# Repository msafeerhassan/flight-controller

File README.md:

# Custom Flight Controller
## A completely custom high-efficiency Flight Controller for Drone.
This flight controller is based on STM32F722RET6 MCU and BMI270 Gyro. This is optimized for modern FPV Drones featuring a 4 layer PCB and a dedicated 8-Pin connecter for modern ESC's.

### Hardware Specifications

MCU: STM32F722RET6

Gyro: BMI270 via Serial Peripheral Interface

Storage: W25NO1G

Input Voltage: 3S-6S LiPo (integrated 5V/2A Regulator)

OSD: AT7456E

Features: Buzzer for emergency situation, USB-C Programming, Suitable capacitors, diodes, inductors and resistors

### ESC Connection Guide
Pin 1 : VBAT : Battery Input

Pin 2 : GND : Ground

Pin 3 : Motor 1 : PB4

Pin 4 : Motor 2 : PB5

Pin 5 : Motor 3 : PB0

Pin 6 : Motor 4 : PB1

Pin 7 : Current : PC0

Pin 8 : Telemetry : PC7

### Software Specifications
Compatible with: 
- Betaflight
- Rotorflight
##### Code is given in firmware folder

### PCB:

### Schematic Diagram:

### Designed by Safeer Hassan :)

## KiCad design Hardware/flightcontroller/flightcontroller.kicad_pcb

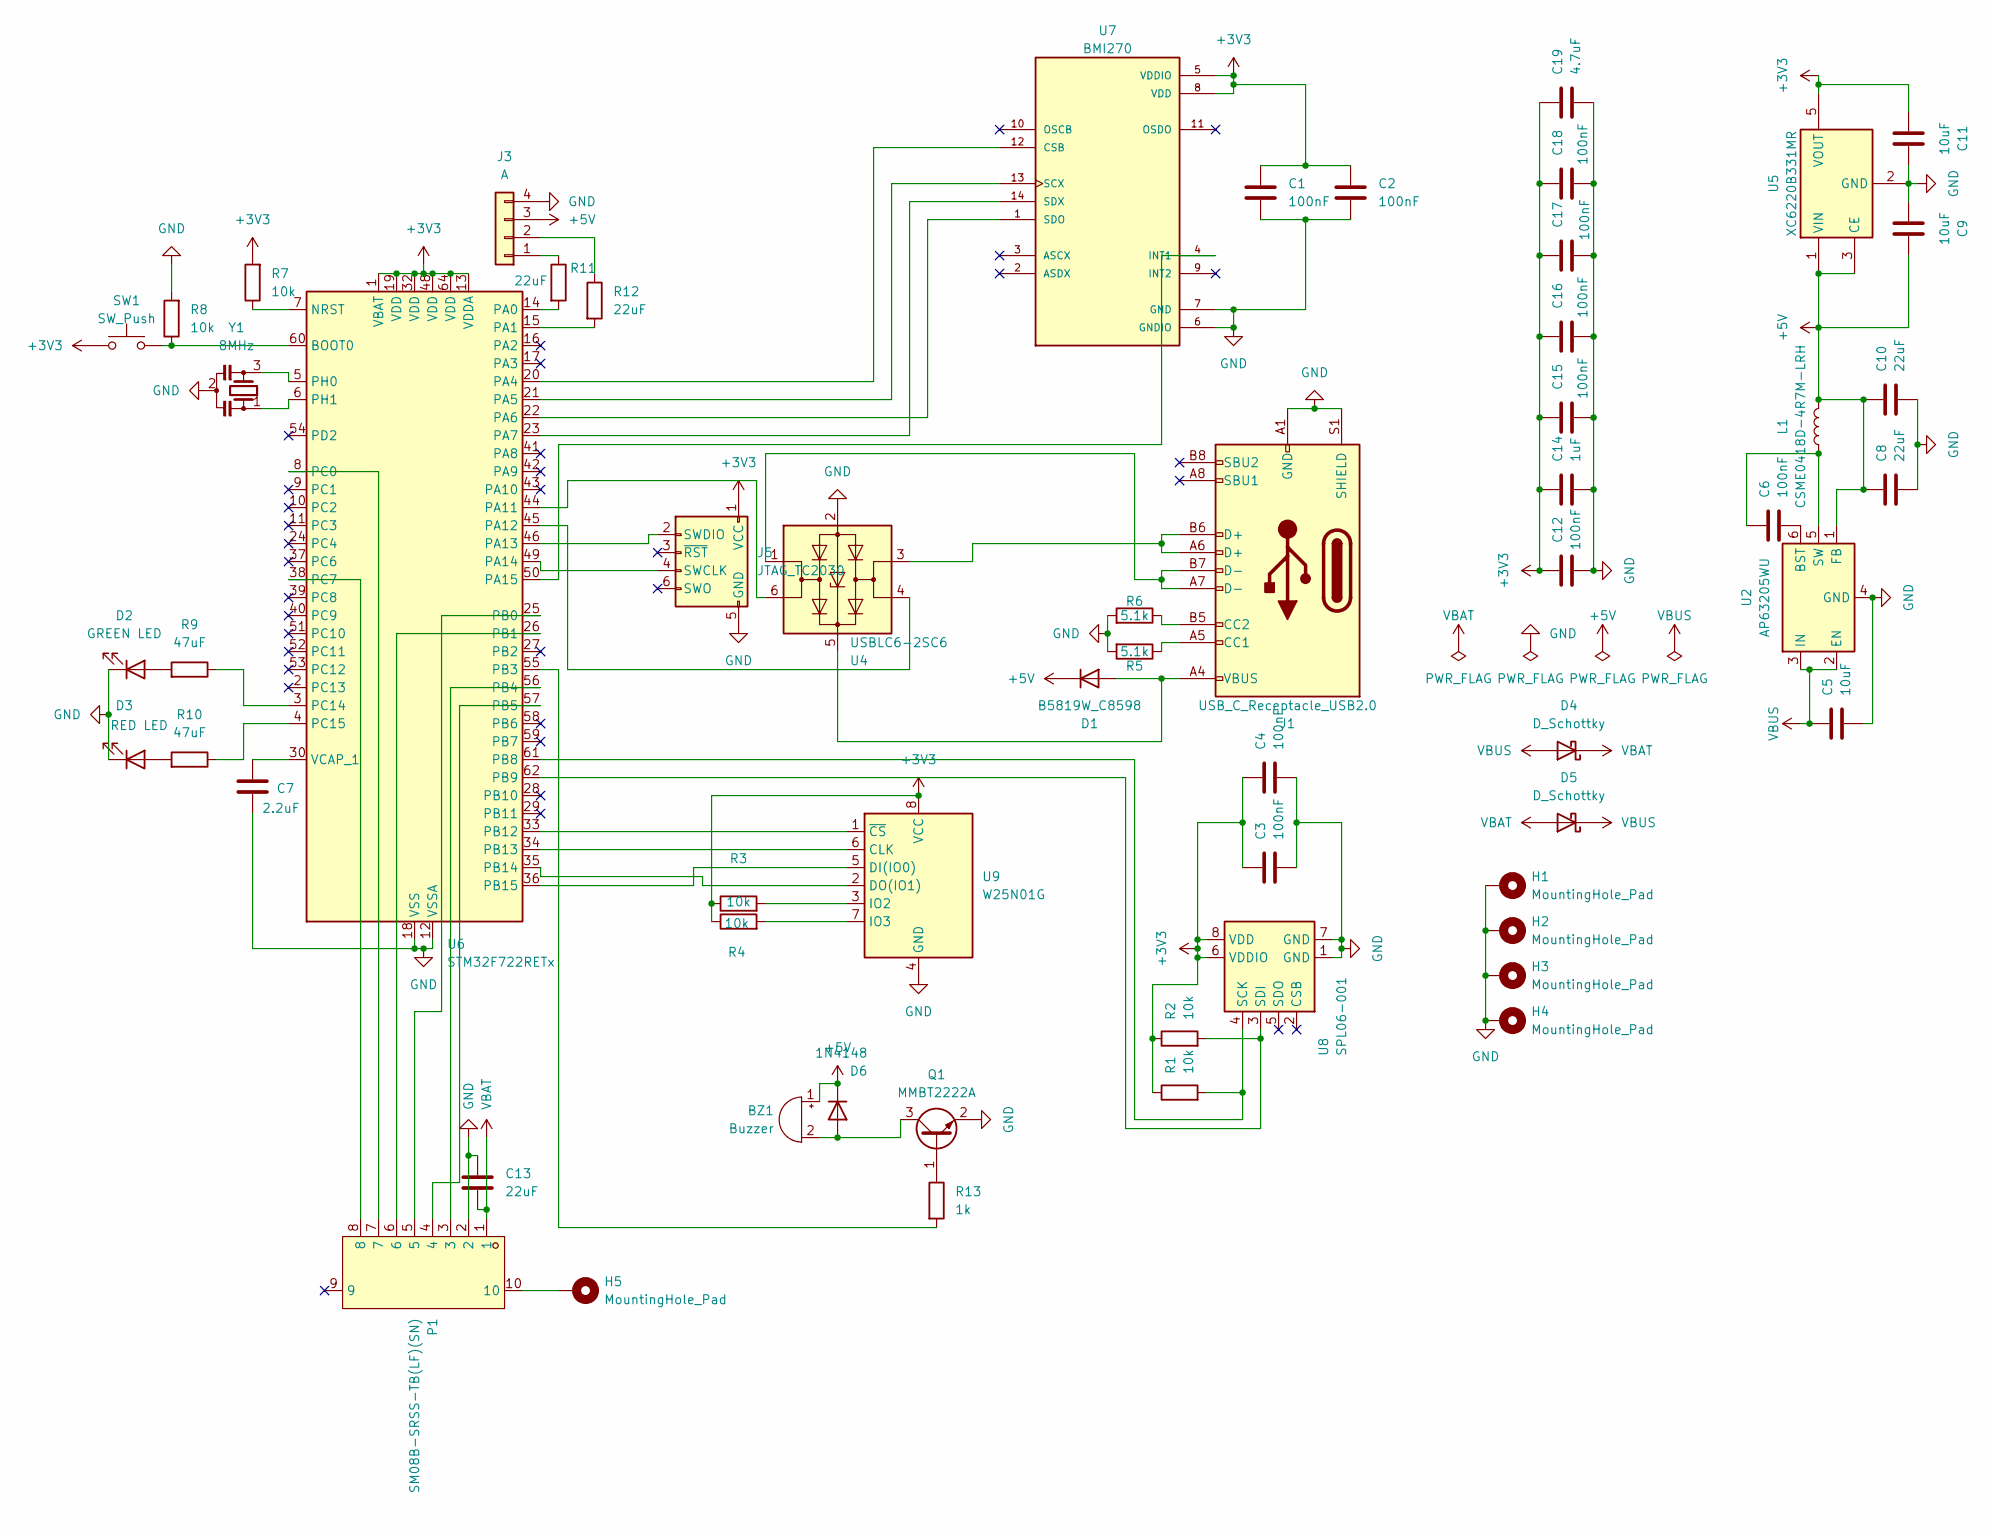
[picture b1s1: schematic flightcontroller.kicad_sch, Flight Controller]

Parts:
BZ1: Buzzer; Buzzer_12x9.5RM7.6
C1, C2, C3, C4, C6, C12, C15, C16, C17, C18: 100nF; C_0603_1608Metric
C5, C9, C11: 10uF; C_0805_2012Metric
C7: 2.2uF; C_0603_1608Metric
C8, C10, C13: 22uF; C_0805_2012Metric
C14: 1uF; C_0603_1608Metric
C19: 4.7uF; C_0805_2012Metric
D1: B5819W_C8598; D_SOD-123
D2: GREEN LED; LED_0603_1608Metric
D3: RED LED; LED_0603_1608Metric
D4, D5: D_Schottky; D_SOD-123
D6: 1N4148; D_DO-35_SOD27_P7.62mm_Horizontal
H1, H2, H3, H4, H5: MountingHole_Pad; MountingHole_3.2mm_M3_Pad_Via
J1: USB_C_Receptacle_USB2.0; USB_C_Receptacle_HRO_TYPE-C-31-M-12
J3: A; JST_GH_BM04B-GHS-TBT_1x04-1MP_P1.25mm_Vertical
J5: JTAG_TC2030; Tag-Connect_TC2030-IDC-NL_2x03_P1.27mm_Vertical
L1: CSME0418D-4R7M-LRH; L_6.3x6.3_H3
P1: SM08B-SRSS-TB(LF)(SN); JST_SHL_SM08B-SHLS-TF_1x08-1MP_P1.00mm_Horizontal; LCSC Part C160407
Q1: MMBT2222A; SOT-23
R1, R2, R3, R4, R7, R8: 10k; R_0603_1608Metric
R5, R6: 5.1k; R_0603_1608Metric
R9, R10: 47uF; C_1210_3225Metric
R11, R12: 22uF; C_0805_2012Metric
R13: 1k; R_0603_1608Metric
SW1: SW_Push; SW_Push_SPST_NO_Alps_SKRK
U2: AP63205WU; TSOT-23-6
U4: USBLC6-2SC6; SOT-23-6
U5: XC6220B331MR; SOT-23-5
U6: STM32F722RETx; LQFP-64_10x10mm_P0.5mm
U7: BMI270; LGA-14_3x2.5mm_P0.5mm_LayoutBorder3x4y
U8: SPL06-001; Bosch_LGA-8_2x2.5mm_P0.65mm_ClockwisePinNumbering
U9: W25N01G; WSON-8-1EP_8x6mm_P1.27mm_EP3.4x4.3mm
Y1: 8MHz; Resonator_SMD_Murata_CSTxExxV-3Pin_3.0x1.1mm

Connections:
+3V3: C1.1, C2.1, C3.1, C4.1, C11.1, C12.1, C14.1, C15.1, C16.1, C17.1, C18.1, C19.1, J5.1 (VCC), R1.1, R2.1, R3.1, R4.1, R7.2, SW1.1, U5.5 (VOUT), U6.1 (VBAT), U6.13 (VDDA), U6.19 (VDD), U6.32 (VDD), U6.48 (VDD), U6.64 (VDD), U7.5 (VDDIO), U7.8 (VDD), U8.6 (VDDIO), U8.8 (VDD), U9.8 (VCC)
+5V: BZ1.1 (+), C8.1, C9.2, C10.1, D1.1 (K), D6.1 (K), J3.3, L1.2, U2.1 (FB), U5.1 (VIN), U5.3 (CE)
GND: C1.2, C2.2, C3.2, C4.2, C5.2, C7.2, C8.2, C9.1, C10.2, C11.2, C12.2, C13.1, C14.2, C15.2, C16.2, C17.2, C18.2, C19.2, D2.1 (K), D3.1 (K), H1.1, H2.1, H3.1, H4.1, J1.A1 (GND), J1.A12 (GND), J1.B1 (GND), J1.B12 (GND), J1.S1 (SHIELD), J3.4, J5.5 (GND), P1.2, Q1.2 (E), R5.2, R6.2, R8.2, U2.4 (GND), U4.2 (GND), U5.2 (GND), U6.12 (VSSA), U6.18 (VSS), U6.31 (VSS), U6.47 (VSS), U6.63 (VSS), U7.6 (GNDIO), U7.7 (GND), U8.1 (GND), U8.7 (GND), U9.4 (GND), Y1.2
unnamed: BZ1.2 (-), D6.2 (A), Q1.3 (C)
unnamed: D1.2 (A), J1.A4 (VBUS), J1.A9 (VBUS), J1.B4 (VBUS), J1.B9 (VBUS), U4.5 (VBUS)
unnamed: D2.2 (A), R9.2
unnamed: D3.2 (A), R10.2
unnamed: H5.1, P1.10
unnamed: J1.A5 (CC1), R5.1
unnamed: J1.B5 (CC2), R6.1
unnamed: J1.A6 (D+), J1.B6 (D+), U4.3 (I/O2)
unnamed: J1.A7 (D-), J1.B7 (D-), U4.1 (I/O1)
unnamed: J3.1, R11.1
unnamed: J3.2, R12.1
unnamed: J5.4 (SWCLK), U6.49 (PA14)
unnamed: J5.2 (SWDIO), U6.46 (PA13)
unnamed: Q1.1 (B), R13.1
unnamed: C6.2, U2.6 (BST)
unnamed: C6.1, L1.1, U2.5 (SW)
unnamed: R8.1, SW1.2, U6.60 (BOOT0)
unnamed: R7.1, U6.7 (NRST)
unnamed: R11.2, U6.14 (PA0)
unnamed: R12.2, U6.15 (PA1)
unnamed: U6.20 (PA4), U7.12 (CSB)
unnamed: U6.21 (PA5), U7.13 (SCX)
unnamed: U6.22 (PA6), U7.1 (SDO)
unnamed: U6.23 (PA7), U7.14 (SDX)
unnamed: U4.6 (I/O1), U6.44 (PA11)
unnamed: U4.4 (I/O2), U6.45 (PA12)
unnamed: U6.50 (PA15), U7.4 (INT1)
unnamed: P1.5, U6.25 (PB0)
unnamed: P1.6, U6.26 (PB1)
unnamed: R13.2, U6.55 (PB3)
unnamed: P1.3, U6.56 (PB4)
unnamed: P1.4, U6.57 (PB5)
unnamed: R1.2, U6.61 (PB8), U8.4 (SCK)
unnamed: R2.2, U6.62 (PB9), U8.3 (SDI)
unnamed: U6.33 (PB12), U9.1 (~CS)
unnamed: U6.34 (PB13), U9.6 (CLK)
unnamed: U6.35 (PB14), U9.2 (DO(IO1))
unnamed: U6.36 (PB15), U9.5 (DI(IO0))
unnamed: P1.7, U6.8 (PC0)
unnamed: P1.8, U6.38 (PC7)
unnamed: R9.1, U6.3 (PC14)
unnamed: R10.1, U6.4 (PC15)
unnamed: U6.5 (PH0), Y1.3
unnamed: U6.6 (PH1), Y1.1
unnamed: C7.1, U6.30 (VCAP_1)
unnamed: R3.2, U9.3 (IO2)
unnamed: R4.2, U9.7 (IO3)
VBAT: C13.2, D4.1 (K), D5.2 (A), P1.1
VBUS: C5.1, D4.2 (A), D5.1 (K), U2.2 (EN), U2.3 (IN)

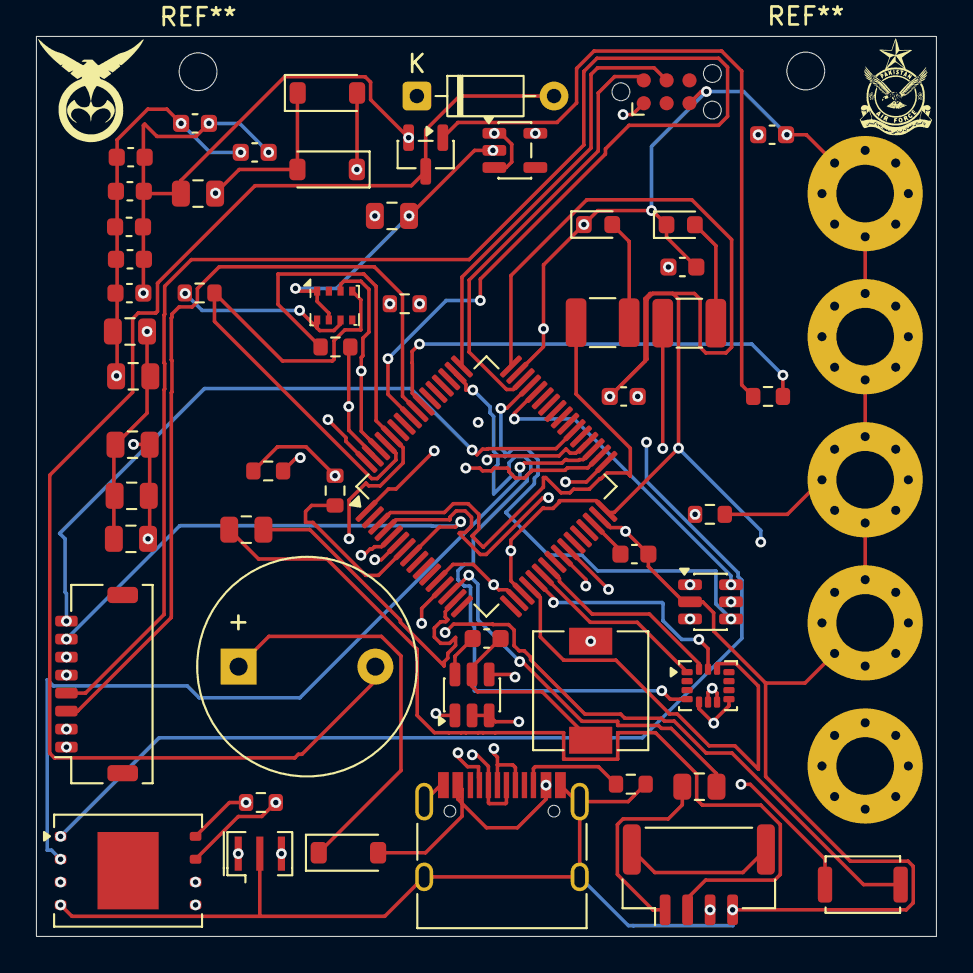
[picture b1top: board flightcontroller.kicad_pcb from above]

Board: 4 copper layers, 50.0 x 50.0 mm, 59 parts (0 on the bottom side), 51 nets.

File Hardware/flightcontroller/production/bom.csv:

Designator,Footprint,Quantity,Value,LCSC Part #
BZ1,Buzzer_12x9.5RM7.6,1,Buzzer,
"C1, C12, C15, C16, C17, C18, C2, C3, C4, C6",0603,10,100nF,
"C10, C13, C8, R11, R12",0805,5,22uF,
"C11, C5, C9",0805,3,10uF,
C14,0603,1,1uF,
C19,0805,1,4.7uF,
C7,0603,1,2.2uF,
D1,D_SOD-123,1,B5819W_C8598,
D2,0603,1,GREEN LED,
D3,0603,1,RED LED,
"D4, D5",D_SOD-123,2,D_Schottky,
D6,D_DO-35_SOD27_P7.62mm_Horizontal,1,1N4148,
J1,USB_C_Receptacle_HRO_TYPE-C-31-M-12,1,USB_C_Receptacle_USB2.0,
J3,JST_GH_BM04B-GHS-TBT_1x04-1MP_P1.25mm_Vertical,1,A,
J5,Tag-Connect_TC2030-IDC-NL_2x03_P1.27mm_Vertical,1,JTAG_TC2030,
L1,L_6.3x6.3_H3,1,CSME0418D-4R7M-LRH,
P1,JST_SHL_SM08B-SHLS-TF_1x08-1MP_P1.00mm_Horizontal,1,SM08B-SRSS-TB(LF)(SN),C160407
Q1,SOT-23,1,MMBT2222A,
"R1, R2, R3, R4, R7, R8",0603,6,10k,
"R10, R9",1210,2,47uF,
R13,0603,1,1k,
"R5, R6",0603,2,5.1k,
SW1,SW_Push_SPST_NO_Alps_SKRK,1,SW_Push,
U2,TSOT-23-6,1,AP63205WU,
U4,SOT-23-6,1,USBLC6-2SC6,
U5,SOT-23-5,1,XC6220B331MR,
U6,LQFP-64_10x10mm_P0.5mm,1,STM32F722RETx,
U7,LGA-14_3x2.5mm_P0.5mm_LayoutBorder3x4y,1,BMI270,
U8,Bosch_LGA-8_2x2.5mm_P0.65mm_ClockwisePinNumbering,1,SPL06-001,
U9,WSON-8-1EP_8x6mm_P1.27mm_EP3.4x4.3mm,1,W25N01G,
Y1,Resonator_SMD_Murata_CSTxExxV-3Pin_3.0x1.1mm,1,8MHz,

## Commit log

2026-01-19 full project commit
2026-01-19 Enhance README with specifications and diagrams
    Added detailed hardware and software specifications, ESC connection guide, and schematic diagram to README.
2026-01-19 Update README with hardware specs and ESC guide
    Added hardware specifications and ESC connection guide to README.
